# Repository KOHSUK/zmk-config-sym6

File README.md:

# Symphonie Nr.6 in F-Dur, op. 68, Pastorale

## License & Attribution

The PMW3610 portion of this PCB design is based on “pmw3610_breakout_for_roBa”  
originally created by kumamuk‑git (https://github.com/kumamuk‑git/roBa/tree/main/pcb/pmw3610_breakout_for_roBa).
© kumamuk‑git. Licensed under GNU General Public License v3.0 (GPL‑3.0).

This modified design (files under `pcb`) is also distributed under GPL‑3.0.  
Corresponding source (KiCad project) is available at:  
https://github.com/KOHSUK/zmk-config-sym6/tree/main/pcb/assemble_right/

See LICENSE (GPL‑3.0) for full terms.

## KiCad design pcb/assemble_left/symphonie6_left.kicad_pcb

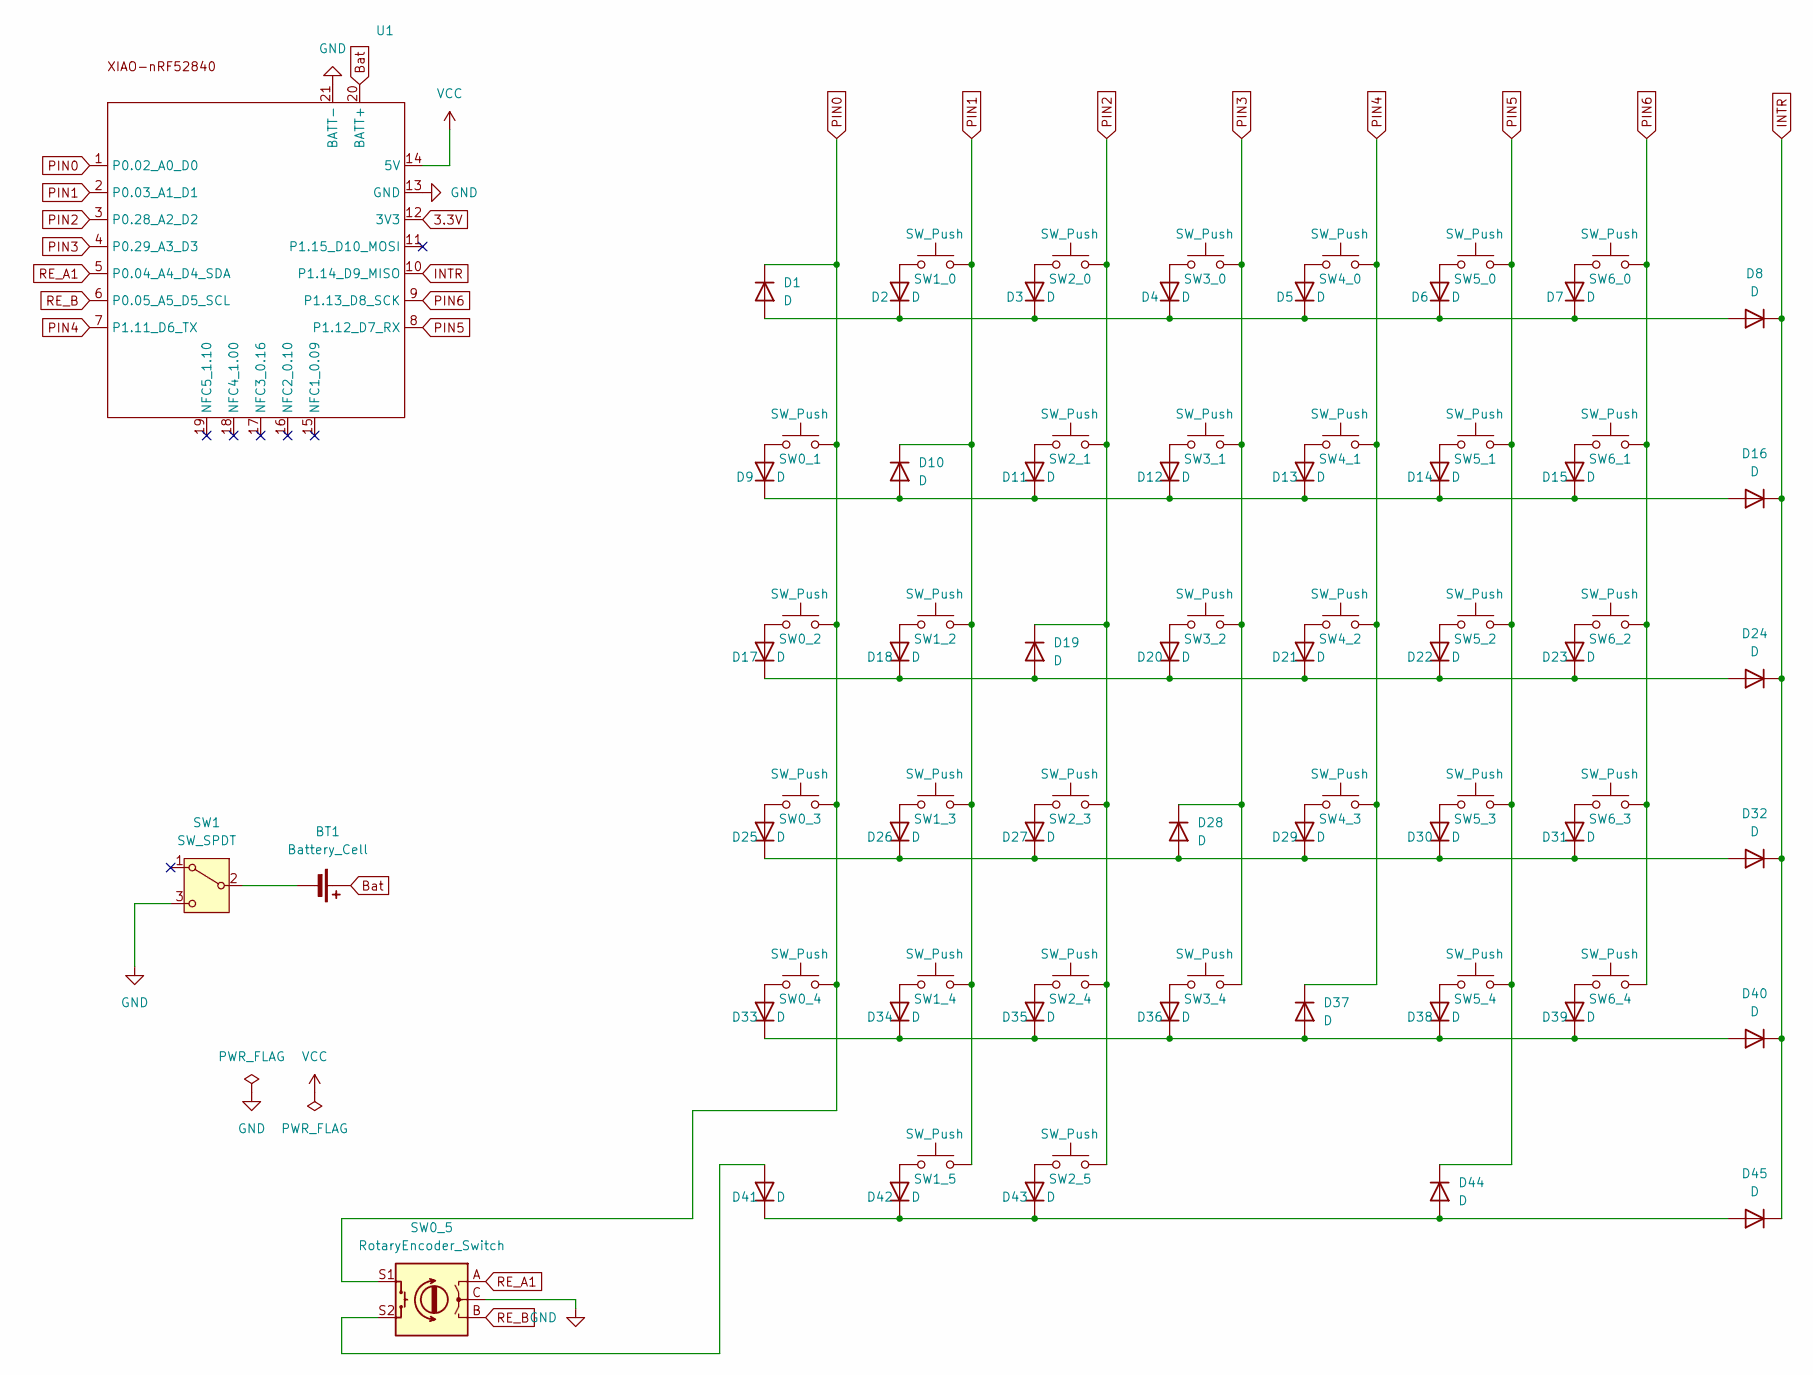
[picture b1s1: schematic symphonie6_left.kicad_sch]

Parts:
BT1: Battery_Cell; JST_S2B-PH-SM4-TB
D1, D2, D3, D4, D5, D6, D7, D8, D9, D10, D11, D12, D13, D14, D15, D16, D17, D18, D19, D20, D21, D22, D23, D24, D25, D26, D27, D28, D29, D30, D31, D32, D33, D34, D35, D36, D37, D38, D39, D40, D41, D42, D43, D44, D45: D; Diode_TH_SMD
SW0_1, SW0_2, SW0_3, SW0_4, SW1_0, SW1_2, SW1_3, SW1_4, SW1_5, SW2_0, SW2_1, SW2_3, SW2_4, SW2_5, SW3_0, SW3_1, SW3_2, SW3_4, SW4_0, SW4_1, SW4_2, SW4_3, SW5_0, SW5_1, SW5_2, SW5_3, SW5_4, SW6_0, SW6_1, SW6_2, SW6_3, SW6_4: SW_Push; Choc_v2_Hotswap_1u
SW0_5: RotaryEncoder_Switch; RotaryEncoder_Alps_EC11E-Switch_Vertical_H20mm
SW1: SW_SPDT; TGSW_MSK-12D19
U1: XIAO_nRF52840_wBAT_wNFC_1

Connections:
3.3V: U1.12 (3V3)
Bat: BT1.1 (+), U1.20 (BATT+)
GND: SW0_5.C, SW1.3 (C), U1.13 (GND), U1.21 (BATT-)
INTR: D8.1 (K), D16.1 (K), D24.1 (K), D32.1 (K), D40.1 (K), D45.1 (K), U1.10 (P1.14_D9_MISO)
unnamed: BT1.2 (-), SW1.2 (B)
unnamed: D1.2 (A), D2.1 (K), D3.1 (K), D4.1 (K), D5.1 (K), D6.1 (K), D7.1 (K), D8.2 (A)
unnamed: D2.2 (A), SW1_0.1
unnamed: D3.2 (A), SW2_0.1
unnamed: D4.2 (A), SW3_0.1
unnamed: D5.2 (A), SW4_0.1
unnamed: D6.2 (A), SW5_0.1
unnamed: D7.2 (A), SW6_0.1
unnamed: D9.2 (A), SW0_1.1
unnamed: D9.1 (K), D10.2 (A), D11.1 (K), D12.1 (K), D13.1 (K), D14.1 (K), D15.1 (K), D16.2 (A)
unnamed: D11.2 (A), SW2_1.1
unnamed: D12.2 (A), SW3_1.1
unnamed: D13.2 (A), SW4_1.1
unnamed: D14.2 (A), SW5_1.1
unnamed: D15.2 (A), SW6_1.1
unnamed: D17.2 (A), SW0_2.1
unnamed: D17.1 (K), D18.1 (K), D19.2 (A), D20.1 (K), D21.1 (K), D22.1 (K), D23.1 (K), D24.2 (A)
unnamed: D18.2 (A), SW1_2.1
unnamed: D20.2 (A), SW3_2.1
unnamed: D21.2 (A), SW4_2.1
unnamed: D22.2 (A), SW5_2.1
unnamed: D23.2 (A), SW6_2.1
unnamed: D25.2 (A), SW0_3.1
unnamed: D25.1 (K), D26.1 (K), D27.1 (K), D28.2 (A), D29.1 (K), D30.1 (K), D31.1 (K), D32.2 (A)
unnamed: D26.2 (A), SW1_3.1
unnamed: D27.2 (A), SW2_3.1
unnamed: D29.2 (A), SW4_3.1
unnamed: D30.2 (A), SW5_3.1
unnamed: D31.2 (A), SW6_3.1
unnamed: D33.2 (A), SW0_4.1
unnamed: D33.1 (K), D34.1 (K), D35.1 (K), D36.1 (K), D37.2 (A), D38.1 (K), D39.1 (K), D40.2 (A)
unnamed: D34.2 (A), SW1_4.1
unnamed: D35.2 (A), SW2_4.1
unnamed: D36.2 (A), SW3_4.1
unnamed: D38.2 (A), SW5_4.1
unnamed: D39.2 (A), SW6_4.1
unnamed: D41.2 (A), SW0_5.S2
unnamed: D41.1 (K), D42.1 (K), D43.1 (K), D44.2 (A), D45.2 (A)
unnamed: D42.2 (A), SW1_5.1
unnamed: D43.2 (A), SW2_5.1
PIN0: D1.1 (K), SW0_1.2, SW0_2.2, SW0_3.2, SW0_4.2, SW0_5.S1, U1.1 (P0.02_A0_D0)
PIN1: D10.1 (K), SW1_0.2, SW1_2.2, SW1_3.2, SW1_4.2, SW1_5.2, U1.2 (P0.03_A1_D1)
PIN2: D19.1 (K), SW2_0.2, SW2_1.2, SW2_3.2, SW2_4.2, SW2_5.2, U1.3 (P0.28_A2_D2)
PIN3: D28.1 (K), SW3_0.2, SW3_1.2, SW3_2.2, SW3_4.2, U1.4 (P0.29_A3_D3)
PIN4: D37.1 (K), SW4_0.2, SW4_1.2, SW4_2.2, SW4_3.2, U1.7 (P1.11_D6_TX)
PIN5: D44.1 (K), SW5_0.2, SW5_1.2, SW5_2.2, SW5_3.2, SW5_4.2, U1.8 (P1.12_D7_RX)
PIN6: SW6_0.2, SW6_1.2, SW6_2.2, SW6_3.2, SW6_4.2, U1.9 (P1.13_D8_SCK)
RE_A1: SW0_5.A, U1.5 (P0.04_A4_D4_SDA)
RE_B: SW0_5.B, U1.6 (P0.05_A5_D5_SCL)
VCC: U1.14 (5V)

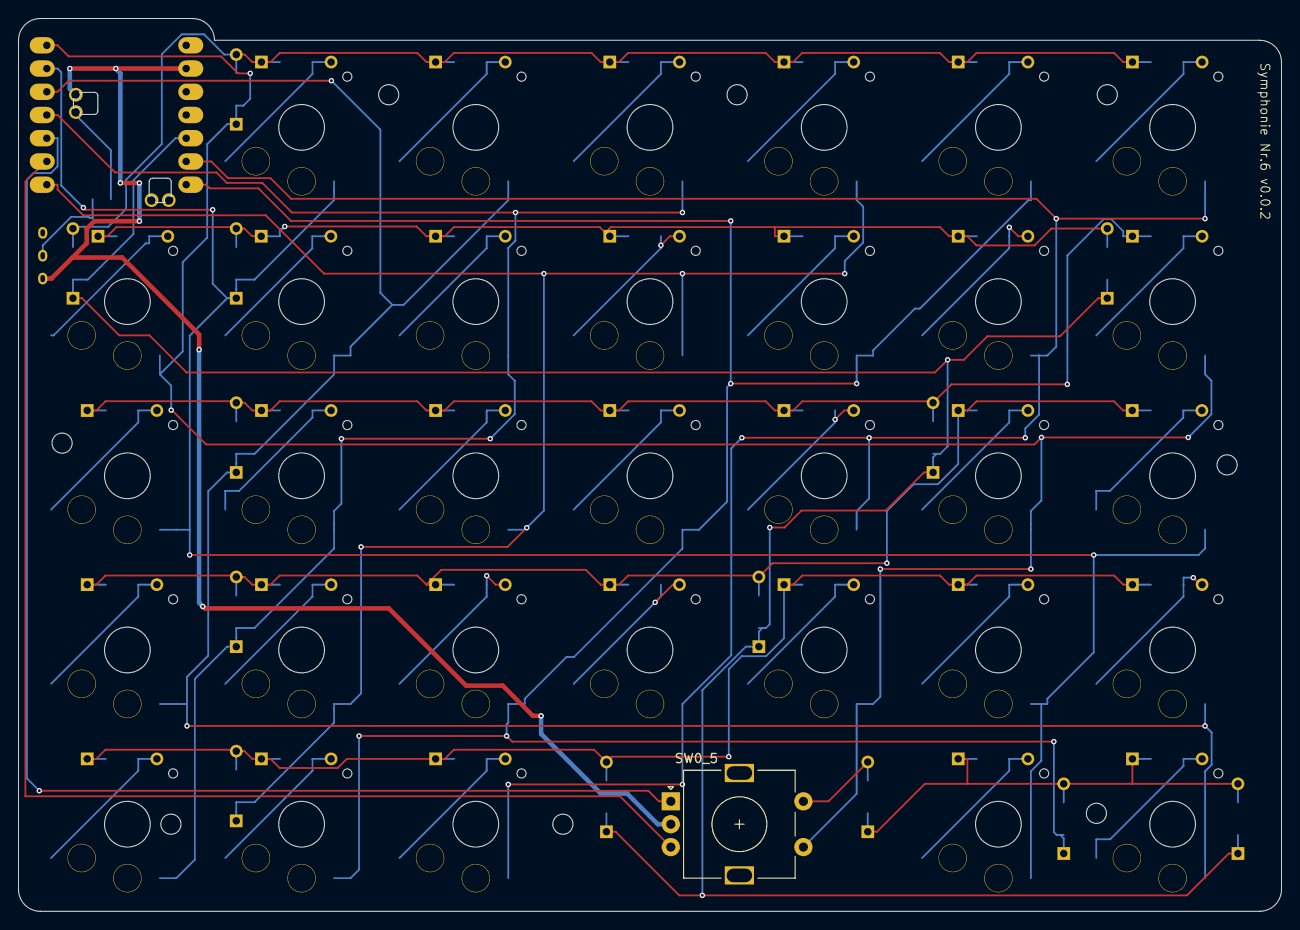
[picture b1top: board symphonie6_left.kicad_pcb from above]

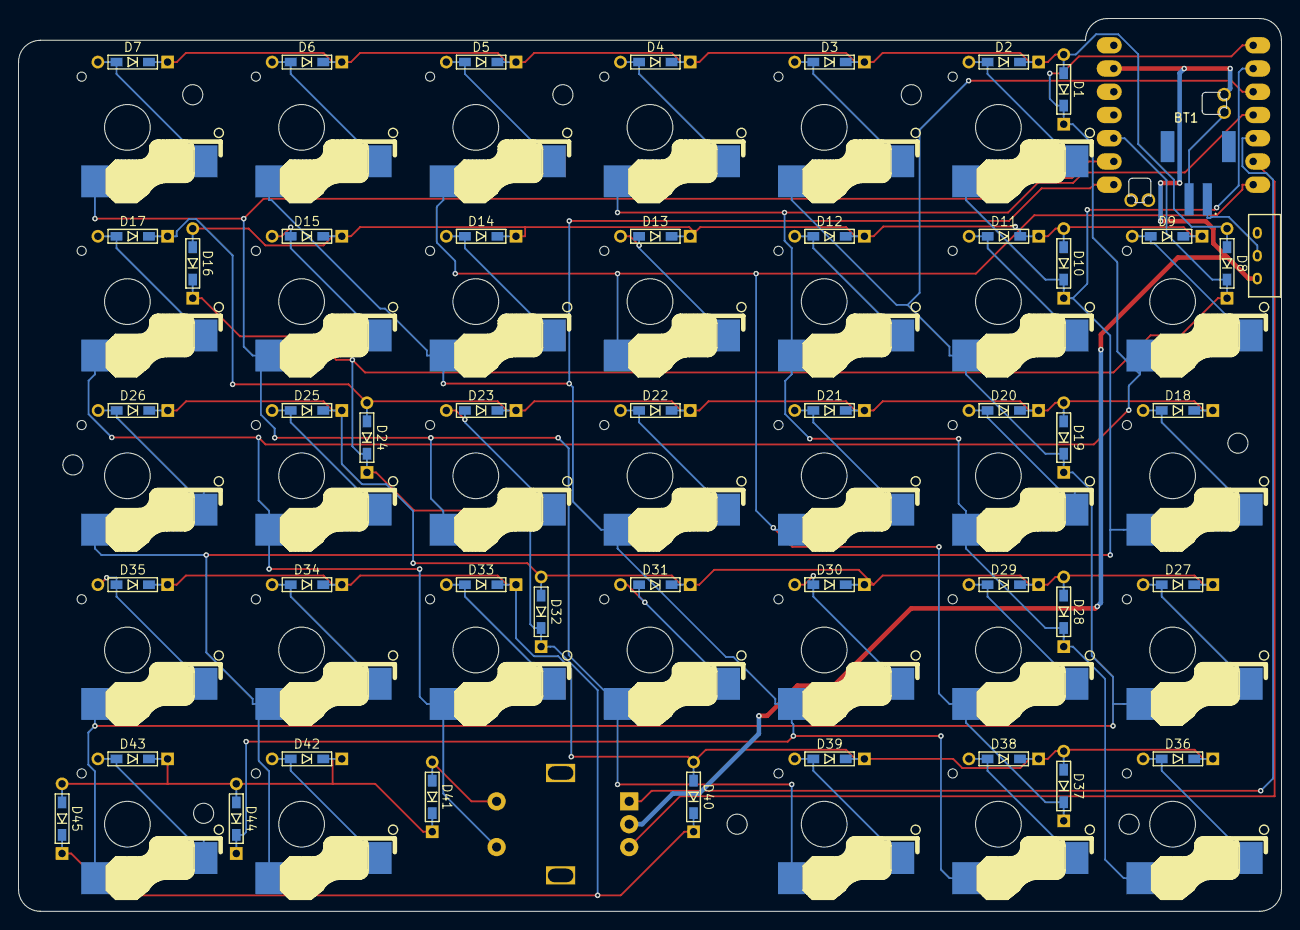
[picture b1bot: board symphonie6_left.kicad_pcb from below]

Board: 2 copper layers, 138.1 x 97.6 mm, 89 parts (2 on the bottom side), 52 nets.

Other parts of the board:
Ref**: Val**; m2_Screw_Hole
Ref**#2, Ref**#3, Ref**#4, Ref**#5, Ref**#6, Ref**#7, Ref**#8: Val**; m2_Screw_Hole

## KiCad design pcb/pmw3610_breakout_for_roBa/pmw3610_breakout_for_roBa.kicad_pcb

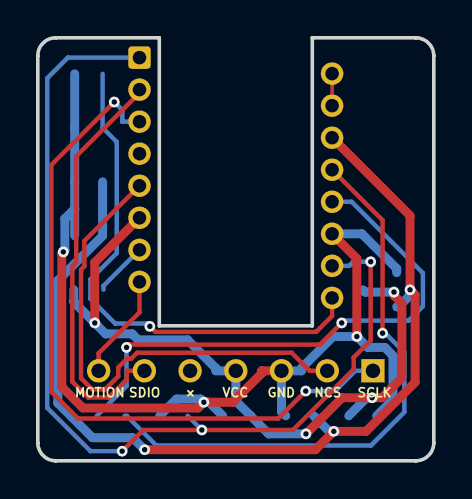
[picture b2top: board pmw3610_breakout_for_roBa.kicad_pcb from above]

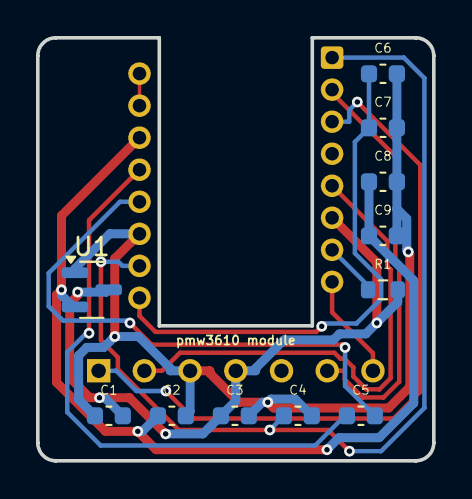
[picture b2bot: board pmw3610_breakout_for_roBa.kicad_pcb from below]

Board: 2 copper layers, 22.0 x 23.5 mm, 13 parts (11 on the bottom side), 13 nets.

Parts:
C1, C2: 1u; C_0603_1608Metric
C3, C8: 100n; C_0603_1608Metric
C4: 10n; C_0603_1608Metric
C5: 100n (X7R); C_0603_1608Metric
C6: 10u (X7R); C_0603_1608Metric
C7: 10n (X7R); C_0603_1608Metric
C9: 3.3u/25V; C_0603_1608Metric
J1: Conn_01x08; pmw3610_connector_b
R1: 2M; R_0603_1608Metric
U1: MCP1700T-1802E/TT; SOT-23
U2: PMW3610; PMW3610DM-SUDU 16Pin

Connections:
+1V9: C2.1, C8.1, C9.1, U1.2 (VO), U2.14 (VDD)
GND: C1.1, C2.2, C3.2, C4.2, C6.2, C7.2, C8.2, C9.2, J1.3, U1.1 (GND), U2.11 (GND)
MOTION: J1.7 (Pin_6), U2.8 (MOTION)
NCS: J1.2, U2.5 (NCS)
unnamed: C4.1, U2.1 (+VCSEL), U2.10 (PASS_T)
unnamed: U2.15 (XYLASER), U2.16 (-VCSEL)
unnamed: C5.1, U2.13 (CN)
unnamed: C5.2, U2.12 (CP)
unnamed: R1.1, U2.7 (NRESET)
unnamed: C6.1, C7.1, U2.9 (VCP)
SCLK: J1.1, U2.3 (SCLK)
SDIO: J1.6, U2.2 (SDIO)
VCC: C1.2, C3.1, J1.4, R1.2, U1.3 (VI), U2.6 (VDDIO)

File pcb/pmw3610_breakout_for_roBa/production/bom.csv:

Designator,Footprint,Quantity,Value,LCSC Part #
C1,0603,1,1u,C14663
C2,0603,1,1u,C15849
"C3, C8",0603,2,100n,C19666
C4,0603,1,10n,C19666
C5,0603,1, 100n (X7R),C19666
C6,0603,1, 10u (X7R),C19666
C7,0603,1, 10n (X7R),C19666
C9,0603,1,3.3u/25V,C19666
J1,pmw3610_connector_b,1,Conn_01x08,
R1,0603,1,2M,
U1,SOT-23,1,MCP1700T-1802E/TT,
U2,PMW3610DM-SUDU 16Pin,1,PMW3610,

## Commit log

2025-03-20 Add configuration and overlay files for Symphonie Nr.6 shield
2025-03-20 Update keymap for Symphonie Nr.6 shield with new layer definitions and bindings
2025-03-20 Add board and shield configurations for Seeeduino Xiao BLE in build.yaml
2025-03-20 fixed overlay files
2025-03-20 fixed a typo in the keymap file.
2025-03-20 Fix missing closing braces in Symphonie Nr.6 keymap file
2025-03-20 added a missing binding expression
2025-03-20 fixed typo in config
2025-03-20 Update Symphonie Nr.6 keymap and GPIO configurations in overlay files
2025-03-20 Add ZMK Studio configuration to Symphonie Nr.6 left board file
2025-03-21 Add kscan and matrix-transform configurations to the chosen node
2025-03-21 Refactor Symphonie Nr.6 configuration: add matrix-transform include and comment out ZMK Studio settings
2025-03-21 Refactor Symphonie Nr.6 DTSI: update chosen node to use physical layout and reorder includes
2025-03-21 Revert "Refactor Symphonie Nr.6 DTSI: update chosen node to use physical layout and reorder includes"
    This reverts commit ca39b4fd505c23ccadda99fa08330dfcc9880e37.
2025-03-21 Revert "Refactor Symphonie Nr.6 configuration: add matrix-transform include and comment out ZMK Studio settings"
    This reverts commit 0871a78244cf1ce6ee615d04fff7542048b8e6bc.
2025-03-21 Revert "Add kscan and matrix-transform configurations to the chosen node"
    This reverts commit 14679f4542d98d3a5011d900e77f0c1926f8a53a.
2025-03-21 Refactor Symphonie Nr.6 overlays: update GPIO configuration for kscan0
2025-03-21 Refactor Symphonie Nr.6 DTSI: update chosen node to use kscan and matrix-transform configurations
2025-03-21 Refactor Symphonie Nr.6 configuration: remove ZMK Studio references from YAML and config files
2025-03-21 Refactor Symphonie Nr.6 layouts: remove unused physical layouts and update configuration for kscan and matrix-transform
2025-03-21 Refactor Symphonie Nr.6 DTSI: disable xiao_serial node
2025-03-21 Refactor Symphonie Nr.6 overlays: update GPIO configurations to include pull-down resistors
2025-03-21 Revert "Refactor Symphonie Nr.6 overlays: update GPIO configurations to include pull-down resistors"
    This reverts commit b9ea86eca23de07c471f807520becbd8ab0391f2.
2025-03-21 Refactor Symphonie Nr.6 DTSI: add debounce and poll period configurations for kscan
2025-03-21 Refactor Symphonie Nr.6 DTSI: fix syntax for debounce and poll period configurations
2025-03-21 Refactor Symphonie Nr.6 DTSI: correct syntax for debounce and poll period configurations
2025-04-18 v0.0.2 pcb
2025-04-18 Refactor Symphonie Nr.6 configuration: update GPIO settings and PMW3610 driver integration of the right side
2025-04-18 Refactor Symphonie Nr.6 DTSI: update keymap to correct column mapping for key matrix
2025-04-20 Refactor Symphonie Nr.6: update keymap bindings and GPIO configuration for left encoder
2025-04-20 Refactor Symphonie Nr.6 configuration: add ZMK Studio settings for right shield
2025-04-20 Refactor Symphonie Nr.6 configuration: update keymap mapping and adjust row offset for right shield
2025-04-20 Refactor Symphonie Nr.6 configuration: enable ZMK Studio and locking settings for right shield
2025-04-20 Refactor Symphonie Nr.6 configuration: adjust build.yaml to enable zmk studio
2025-04-20 Refactor Symphonie Nr.6 keymap: correct binding for space key in default layer
2025-04-20 fixed: physical layout
2025-04-25 Refactor Symphonie Nr.6 keymap: update default layer bindings and fn2 layer functionality
2025-04-27 Refactor Symphonie Nr.6 keymap: update fn1 layer bindings for mouse keys
2025-04-28 Refactor Symphonie Nr.6 configuration: update PMW3610 inversion settings and comment out automouse and scroll layers
2025-04-28 Refactor Symphonie Nr.6 configuration: enable automouse and scroll layers in overlay, add battery reporting settings in right config
2025-04-28 Refactor Symphonie Nr.6 configuration: comment out automouse and scroll layers in trackball settings
2025-04-28 Refactor Symphonie Nr.6 keymap and overlay: adjust mouse key bindings and update scroll layer configuration
2025-06-06 feat: added several 3D models
2025-06-06 Refactor Symphonie Nr.6 keymap and overlay: correct key bindings and enable automouse layer
2025-06-06 Refactor Symphonie Nr.6 keymap: correct LSHFT key bindings in default layer
